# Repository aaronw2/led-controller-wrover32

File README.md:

# led-controller-wrover32
Wrover32 based LED controller for NeoPixels and DotStars with 5v signalling
and micro SD

Power:

This board is powered by 5V and generates a 3.3V supply via U1.  This board
may draw up to 500ma of current at 5V.  The 3.3V supply is capable of
generating up to 1A.

This board makes use of a Torex Semiconductor XCL220 micro DC/DC converter
to efficiently provide 3.3v of power.  This inexpensive device is reportedly
93% efficient which should increase battery life and reduce heat buildup.

Do not draw more than 500ma from any single power or ground pin on J2 or J4.

On J5, VBUS is 5V as are pins 9 and 12 on J4 and pin 1 on J2.
J6 and J7 also provide +5V at the + terminal.

5V may be shunted through the board, but limit the current to no more than 2A.

5V may be supplied by any pin, however power provided by the micro SD
connector J3 should be limited to 500 ma.

USB:

There are two USB connectors on the board for programming.  The Micro USB
connector J3 or J5 may be used.  Do not use both connectors.  J5 is designed
so either a 4 pin header or a USB cable can be soldered to the board,
eliminating the need to use micro USB.

The USB port is connected to a SI Labs CP2102 USB to serial UART for
programming and debugging purposes.

I/O:

Unlike most if not all other ESP32 based boards, this board includes a
3V to 5V bidirectional level shifter for IO25, IO26, IO32 and IO33.  These
I/O ports can also be driven by the RTC in the ESP32 to help offload driving
NeoPixels.

I/O27 is connected to an on-board SK6812MINI RGB NeoPixel with the output
connected to J2 pin 4.

Connectors:

J1: Micro SD connector

J2:
1 - VBUS (+5V)
2 - GND
3 - +3.3V
4 - DO - Output from on-board NeoPixel
5 - IO34
6 - IO33_H - IO33 at 5v signalling
7 - IO32_H - IO32 at 5V signalling
8 - IO18_H - IO18 at 5V signalling
9 - IO5_H - IO5 at 5V signalling
10 - SENSOR_VN - Input to Sensor_VN pin
11 - SENSOR_VP - Input to Sensor_VP pin
12 - Reset

J3: Micro USB connector

J4:
1 - IO23 (10K pullup)
2 - IO22 (10K pullup)
3 - IO21 (10K pullup)
4 - IO19
5 - IO26
6 - IO25
7 - IO35
8 - IO0
9 - +3.3V
10 - GND
11 - GND
12 - VBUS (+5V)

J5: USB
1 - VBUS (+5) (3A input capable)
2 - D-
3 - D+
4 - GND

J6:
1 - GND
2 - VBUS (+5V)

J7:
1 - GND
2 - VBUS (+5V)
3 - FET connected to ground, driven by IO26 (max 1A, 12V)

J8:
1 - GND
2 - IO23 (pullup) same as J4-1
3 - IO22 (pullup) same as J4-2
4 - IO21 (pullup) same as J4-3
5 - +3.3V

J9:
1 - GND
2 - +5V (3A input capable)

J11:
1 - Speaker +
2 - Speaker -

J101:
Note: pins 1 and 2 are the opposite of other power connectors
1 - +12V 400ma
2 - GND

I2C:
I2C is supported on pins IO21, IO22 and IO23, though one of those pins can
also be used for a shared interruput line.

Notes:
Some pins serve multiple purposes.  For example, two of the 5V I/O pins are
shared.  For example, IO5 is also connected to the FET for PWM and IO33 is
also connected to the BCLK on the amplifier.  If these are used, do not use
the 5V I/Os for IO5 and/or IO33.  If IO33 is used, do not hook up a speaker.

IO18 and IO32 are dedicated for 5V I/O and IO27 is dedicated for the status
LED and the output of that is useable for driving WS2812s or compatible 24-bit
LEDs.

Power:

This board uses a Torex Semiconductor XCL220 buck converter to efficiently
generate 3.3v with an output capability of up to 1A.  It supports automatic
shutdown for thermal, overcurrent and under voltage events.

Any VBUS (+5V) pin many be used to deliver or draw 5V from the board.  Total
current should not exceed 2A for all combined ground and +5V pins, however
for power input connectors J5 and J9 are capable of handling 3A in order to
supply the 12V booster

Ground:
Any GND pin can be used for ground.

+3.3V
The on-board power supply is capable of generating up to 1A.  The Wrover32 can
consume up to 500ma.  Please limit power consumption to no more than 200ma to
be safe.

+12V
This board includes a 5V to 12V boost circuit in order to provide power to
a fan or other accessories via J101.  Do not exceed 400ma.  All components
needed for the 12V boost circuit start at reference 100.  To disable 12V
support, do not install any components in this range, i.e. J101, R101, etc.

RESET:

This board can be reset in one of three ways.  The serial UART, SW1 and J2
pin 12 can all be used to reset the board.  To reset the board using J2,
pull the RESET line to ground.

5V logic

This board is designed to be able to drive 5 channels of NeoPixels, or two
channels of DotStars and one channel of NeoPixels.  One NeoPixel (D1) is
built-in to the board and the output is connected to J2 pin 4.  The other
four channels are pins J2 6, 7, 8 and 9.  Note that D1 uses a WS2813B-Mini.

Connectors J2 and J4:

Connectors J2 and J4 and JST VM12B-SRSS-TB connectors and mate with the
JST 12SR-3S connector.  These connectors can be found at Digikey, including
connectors with wires already installed. Note that the wire for the mating
connectors is a bit hard to find. Alpha Wire 2928 WH005 fits this connector.
It is a bit pricy. Mouser has it cheaper than Digikey for $35/100 feet,
though I also found it online for $25. The connector requires 7 strand wire
with an outer diameter between 0.54 and 0.58mm.

Connectors J5 and J101 are JST PH series connectors which are readily
available. J101 is not at all uncommon for computer fans.

All other connectors are pin headers with 1.27mm pitch, which is half the
normal 2.54mm pitch except for J9, which uses the 2.54mm pitch.

USB:
Use either a micro USB cable OR J5, do not use both for USB I/O.  Both,
however, are safe for power and ground, however do not exceed 900ma
when using a micro USB cable.

Microphone:

An optional SPH0645LM4H-B i2s compatible microphone is available.
If present, it is configured for the left channel.  Word-select is on IO5,
clock is on IO0 and data is on IO35.

Fan control:
The PWM pin is not near the 12v supply due to routing issues.  In order to
use PWM support, the fan must be connected to +12 or +5 and the PWM pin
(J7 pin 3) for ground. Note that J7 pin 3 should never be shorted to ground
as this will cause Q4 to act as a diode and likely burn up.

Booting and programming:
This follows the model used on the Wrover development board where DTR and
RTS are used to control IO0, IO2 and RESET.  Note that revision 1.5 and later
fixes the programming by supporting IO2.  IO2 is new for the Wrover32 and is
not used by the Wroom32.

GPIOs:
IO0: I2S-BCLK, RTS for programming, J4-8
IO2: SD-DAT0, RTS for programming
IO4: SD-DAT1
IO5: 5V I/O, FAN PWM
IO12: SD-DAT2
IO13: SD-DAT3/CD
IO14: SD-Clock
IO15: SD-Command
IO16: do not use
IO17: do not use
IO18: 5V I/O
IO19: mic I2S-WS, JU4-4
IO21: Pull-up, J4-3, SDA
IO22: Pull-up, J4-2, SCL
IO23: Pull-up, J4-1, /INT
IO25: J4-6, Speaker DIN
IO26: J4-5, Speaker BCLK
IO27: Status RGB LED output
IO32: 5V I/O
IO33: 5V I/O, Speaker LRCLK
IO34: J2-5 (input only)
IO35: MIC I2S-data in, J4-7
SENSOR_VP: J2-11
SENSOR_VN: J2-10

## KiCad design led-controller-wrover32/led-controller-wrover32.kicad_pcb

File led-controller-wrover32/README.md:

ESP32-Wrover I/Os

IO0: (reset/program), J4-8, MIC-BCLK
IO2: (reset/program), SD DAT0
IO4: SD DAT1
IO5: +5V I/O, FAN PWM
IO12: SD DAT2
IO13: SD DAT3/CD
IO14: SD CLK
IO15: SD CMD
IO16: DNC
IO17: DNC
IO18: +5V I/O
IO19: J4-4, MIC WS
IO21: I2C/INT, J4-3
IO22: I2C/INT, J4-2
IO23: I2C/INT, J4-1
IO25: J4-6, SPKR-DIN
IO26: J4-5, SPKR-BCLK
IO27: NeoPixel
IO32: +5V
IO33: +5V, SPKR-LRCLK
IO34: (input only) J2-5
IO35: (input only) J4-7, MIC-OUT
SENSOR_VP: J2-11
SENSOR_VN: J2-10
RXD0:
TXD0:
EN:

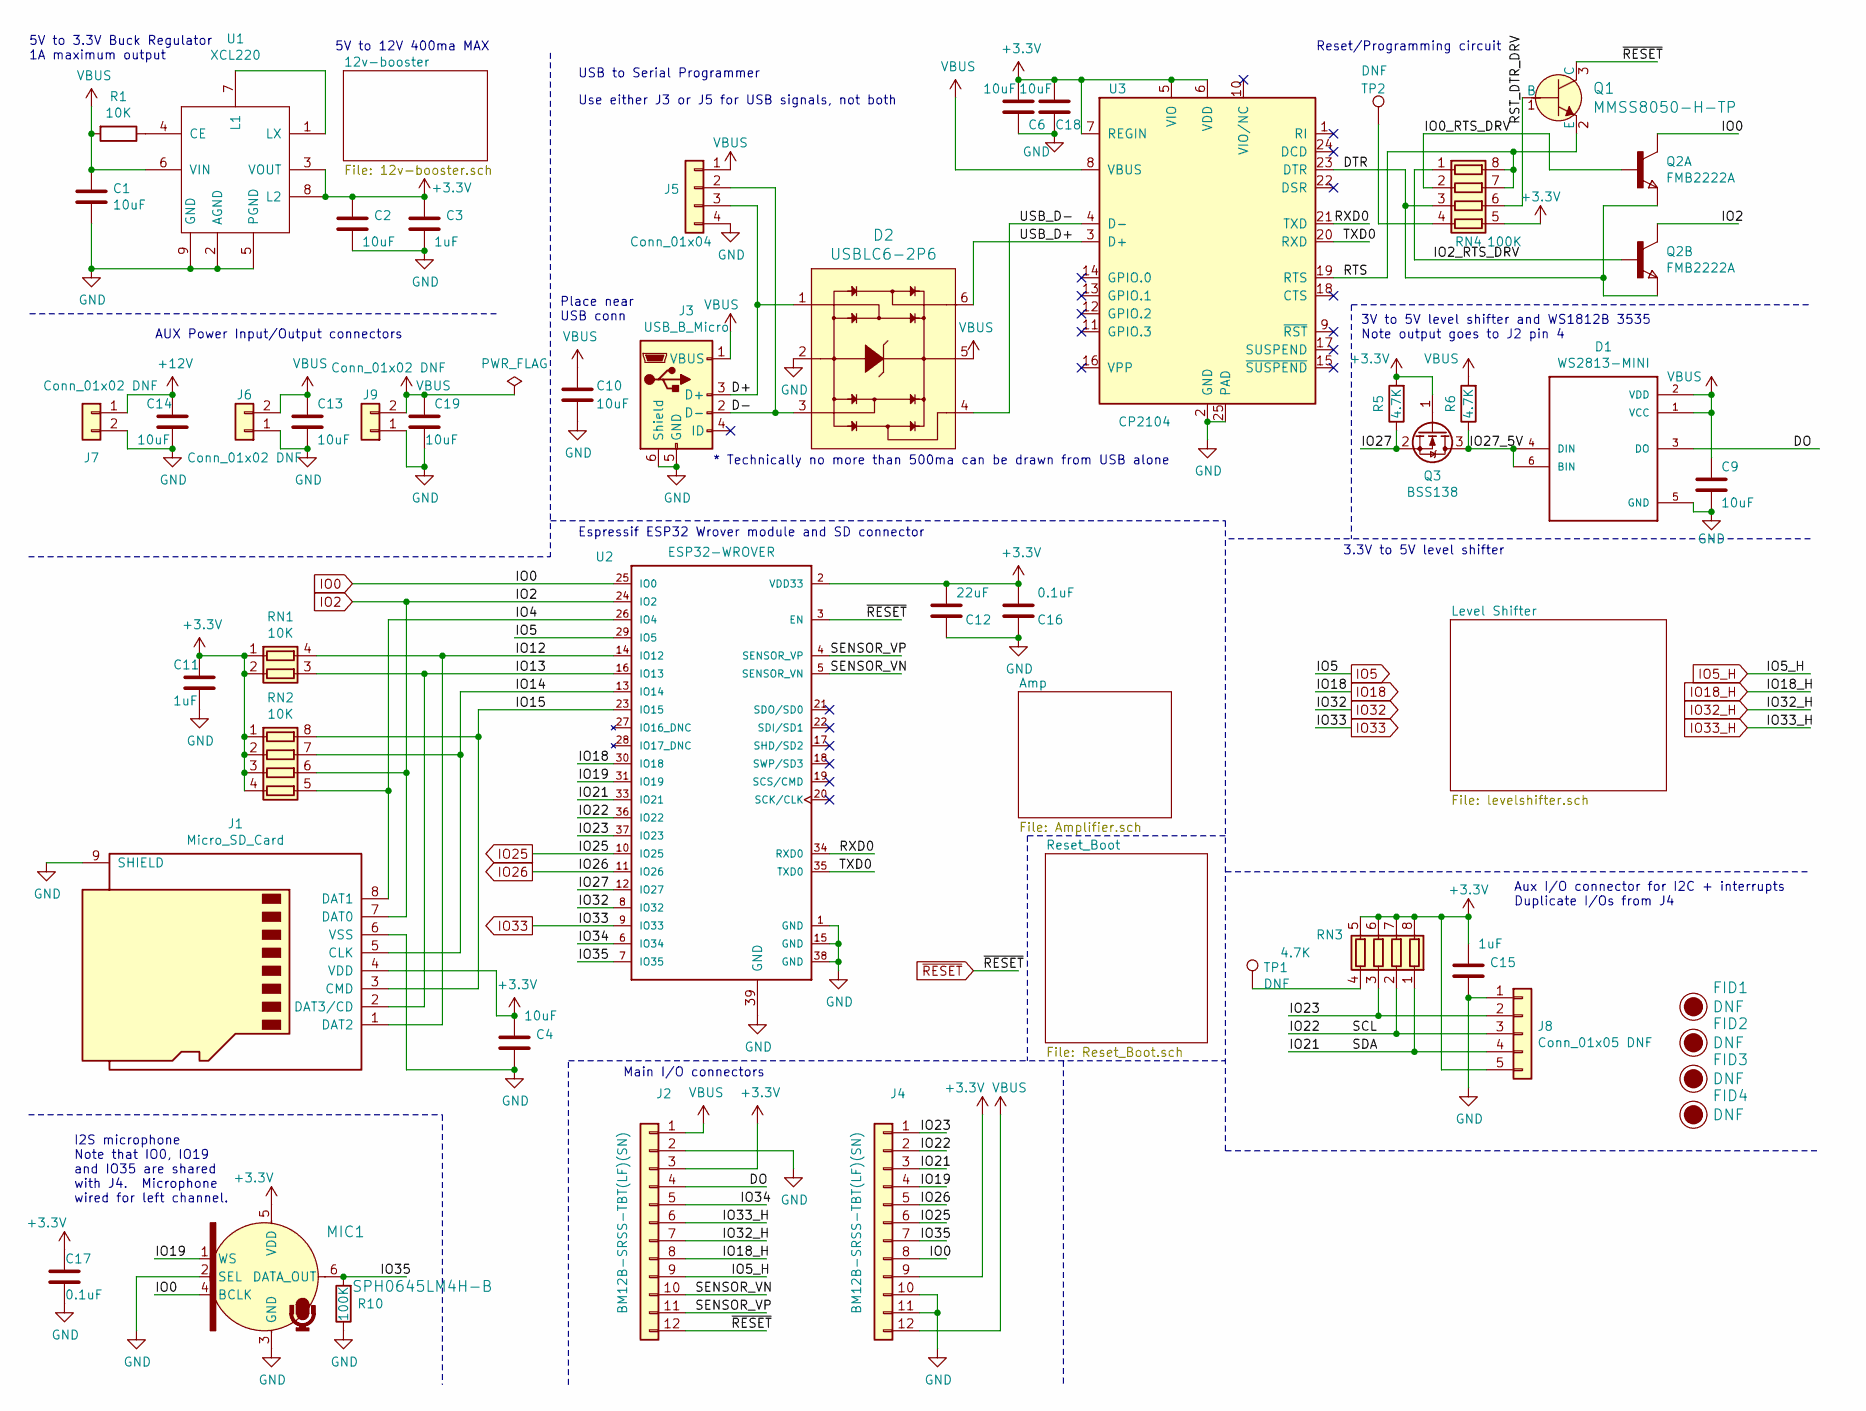
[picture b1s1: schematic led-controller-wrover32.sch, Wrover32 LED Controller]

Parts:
C1: 10uF; C_0805_2012Metric; Tolerance 20%; Minimum Voltage 10; MPN CL21B106KOQNNNE
C2, C4, C6, C9, C10, C13, C14, C18, C19: 10uF; C_0805_2012Metric; MPN CL21B106KOQNNNE
C3, C11, C15: 1uF; C_0603_1608Metric; MPN CL10B105KP8NNNC
C12: 22uF; C_0805_2012Metric; MPN CL21A226KPCLRNC
C16, C17: 0.1uF; C_0603_1608Metric; MPN GCM188R71H104KA57D
D1: WS2813-MINI; LED_WS2813-MINI-2; MPN WS2813B-Mini
D2: USBLC6-2P6; SOT-666; MPN USBLC6-2P6; Digi-Key_PN 497-5026-1-ND
FID1, FID2, FID3, FID4: DNF; Fiducial_0.5mm_Mask1mm
J1: Micro_SD_Card; microSD_HC_Wuerth_693072010801; MPN 693072010801
J2, J4: BM12B-SRSS-TBT(LF)(SN); BM12B-SRSS-TB; MPN BM12B-SRSS-TBT(LF)(SN)
J3: USB_B_Micro; USB_Micro-B_Molex-105017-0001; MPN 1050170001
J5: Conn_01x04; JST_PH_B4B-PH-K_1x04_P2.00mm_Vertical; MPN B4B-PH-K-S(LF)(SN)
J6, J7: Conn_01x02 DNF; PinHeader_1x02_P1.27mm_Vertical; MPN TMS-102-01-G-S
J8: Conn_01x05 DNF; PinHeader_1x05_P1.27mm_Vertical; MPN TMS-105-01-G-S
J9: Conn_01x02 DNF; PinHeader_1x02_P2.54mm_Vertical
MIC1: SPH0645LM4H-B; MPN SPH0645LM4H-B; Digi-Key_PN 423-1405-1-ND
Q1: MMSS8050-H-TP; SOT-23; MPN MMSS8050-H-TP; Digi-Key_PN MMSS8050-H-TPMSCT-ND
Q2: FMB2222A; SOT-23-6; MPN FMB2222A
Q3: BSS138; SOT-23; MPN BSS138
R1: 10K; R_0603_1608Metric; Tolerance 5%; MPN CRCW060310K0FKEC
R5, R6: 4.7K; R_0603_1608Metric; MPN CR0603-FX-4701ELF
R10: 100K; R_0603_1608Metric; MPN CRCW0603100KJNEA
RN1: 10K; R_Array_Convex_2x0603; MPN EXB-V4V103JV
RN2: 10K; R_Array_Convex_4x0603; MPN EXB-V8V103JV
RN3: 4.7K; R_Array_Convex_4x0603; MPN CAT16-4701F4LF
RN4: 100K; R_Array_Convex_4x0603; MPN EXB-V8V104JV
TP1, TP2: DNF; TestPoint_Pad_D1.0mm
U1: XCL220; CL-2025-02; MPN XCL220B333FR-G
U2: ESP32-WROVER; ESP32-WROOVER; MPN ESP32-WROVER (16MB)
U3: CP2104; QFN-24-1EP_4x4mm_P0.5mm_EP2.6x2.6mm; MPN CP2104-F03-GMR

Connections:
+3V3: C2.1, C3.1, C4.1, C6.1, C11.1, C12.1, C15.1, C16.1, C17.1, C18.1, J1.4 (VDD), J2.3, J4.9, J8.5, MIC1.5 (VDD), Q3.1 (G), R5.2, RN1.1 (R1.1), RN1.2 (R2.1), RN2.1 (R1.1), RN2.2 (R2.1), RN2.3 (R3.1), RN2.4 (R4.1), RN3.5 (R4.2), RN3.6 (R3.2), RN3.7 (R2.2), RN3.8 (R1.2), RN4.5 (R4.2), U1.3 (VOUT), U1.8 (L2), U2.2 (VDD33), U3.5 (VIO), U3.6 (VDD), U3.7 (REGIN); also elsewhere on the board
+12V: C14.1, J7.1; also elsewhere on the board
/D+: D2.1, J3.3 (D+), J5.3
/D-: D2.3, J3.2 (D-), J5.2
/DO: D1.3 (DO), J2.4
/DTR: Q2.2 (E), Q2.5 (E), RN4.3 (R3.1), U3.23 (DTR)
/IO0_RTS_DRV: Q2.1 (B), RN4.2 (R2.1)
/IO2_RTS_DRV: Q2.3 (B), RN4.1 (R1.1)
/IO4: J1.8 (DAT1), RN2.5 (R4.2), U2.26 (IO4)
/IO12: J1.1 (DAT2), RN1.4 (R1.2), U2.14 (IO12)
/IO13: J1.2 (DAT3/CD), RN1.3 (R2.2), U2.16 (IO13)
/IO14: J1.5 (CLK), RN2.7 (R2.2), U2.13 (IO14)
/IO15: J1.3 (CMD), RN2.8 (R1.2), U2.23 (IO15)
/IO19: J4.4, MIC1.1 (WS), U2.31 (IO19)
/IO21: J4.3, J8.4, RN3.1 (R1.1), U2.33 (IO21)
/IO22: J4.2, J8.3, RN3.2 (R2.1), U2.36 (IO22)
/IO23: J4.1, J8.2, RN3.3 (R3.1), U2.37 (IO23)
/IO27: Q3.2 (S), R5.1, U2.12 (IO27)
/IO27_5V: D1.4 (DIN), D1.6 (BIN), Q3.3 (D), R6.1
/IO34: J2.5, U2.6 (IO34)
/IO35: J4.7, MIC1.6 (DATA_OUT), R10.2, U2.7 (IO35)
/RST_DTR_DRV: Q1.1 (B), RN4.6 (R3.2)
/RTS: Q1.2 (E), RN4.7 (R2.2), RN4.8 (R1.2), U3.19 (RTS)
/RXD0: U2.34 (RXD0), U3.21 (TXD)
/SENSOR_VN: J2.10, U2.5 (SENSOR_VN)
/SENSOR_VP: J2.11, U2.4 (SENSOR_VP)
/TXD0: U2.35 (TXD0), U3.20 (RXD)
/USB_D+: D2.6, U3.3 (D+)
/USB_D-: D2.4, U3.4 (D-)
GND: C1.2, C2.2, C3.2, C4.2, C6.2, C9.2, C10.2, C11.2, C12.2, C13.2, C14.2, C15.2, C16.2, C17.2, C18.2, C19.2, D1.5 (GND), D2.2, J1.6 (VSS), J1.9 (SHIELD), J2.2, J3.5 (GND), J3.6 (Shield), J4.10, J4.11, J5.4, J6.1, J7.2, J8.1, J9.1, MIC1.2 (SEL), MIC1.3 (GND), R10.1, U1.2 (AGND), U1.5 (PGND), U1.9 (GND), U2.1 (GND), U2.15 (GND), U2.38 (GND), U2.39 (GND), U3.2 (GND), U3.25 (PAD); also elsewhere on the board
IO0: J4.8, MIC1.4 (BCLK), Q2.6 (C), U2.25 (IO0); also elsewhere on the board
IO2: J1.7 (DAT0), Q2.4 (C), RN2.6 (R3.2), U2.24 (IO2); also elsewhere on the board
IO5: U2.29 (IO5); also elsewhere on the board
IO5_H: J2.9; also elsewhere on the board
IO18: U2.30 (IO18); also elsewhere on the board
IO18_H: J2.8; also elsewhere on the board
IO25: J4.6, U2.10 (IO25); also elsewhere on the board
IO26: J4.5, U2.11 (IO26); also elsewhere on the board
IO32: U2.8 (IO32); also elsewhere on the board
IO32_H: J2.7; also elsewhere on the board
IO33: U2.9 (IO33); also elsewhere on the board
IO33_H: J2.6; also elsewhere on the board
unnamed: R1.1, U1.4 (CE)
unnamed: RN3.4 (R4.1), TP1.1
unnamed: RN4.4 (R4.1), TP2.1
unnamed: U1.1 (LX), U1.7 (L1)
VBUS: C1.1, C9.1, C10.1, C13.1, C19.1, D1.1 (VCC), D1.2 (VDD), D2.5, J2.1, J3.1 (VBUS), J4.12, J5.1, J6.2, J9.2, R1.2, R6.2, U1.6 (VIN), U3.8 (VBUS); also elsewhere on the board
~RESET: J2.12, Q1.3 (C), U2.3 (EN); also elsewhere on the board

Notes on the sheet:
3.3V to 5V level shifter
Place near USB conn
5V to 3.3V Buck Regulator 1A maximum output
AUX Power Input/Output connectors
USB to Serial Programmer
Use either J3 or J5 for USB signals, not both
* Technically no more than 500ma can be drawn from USB alone
Reset/Programming circuit
I2S microphone Note that IO0, IO19 and IO35 are shared with J4. Microphone wired for left channel.
Main I/O connectors
Aux I/O connector for I2C + interrupts Duplicate I/Os from J4
Espressif ESP32 Wrover module and SD connector
5V to 12V 400ma MAX
3V to 5V level shifter and WS1812B 3535 Note output goes to J2 pin 4

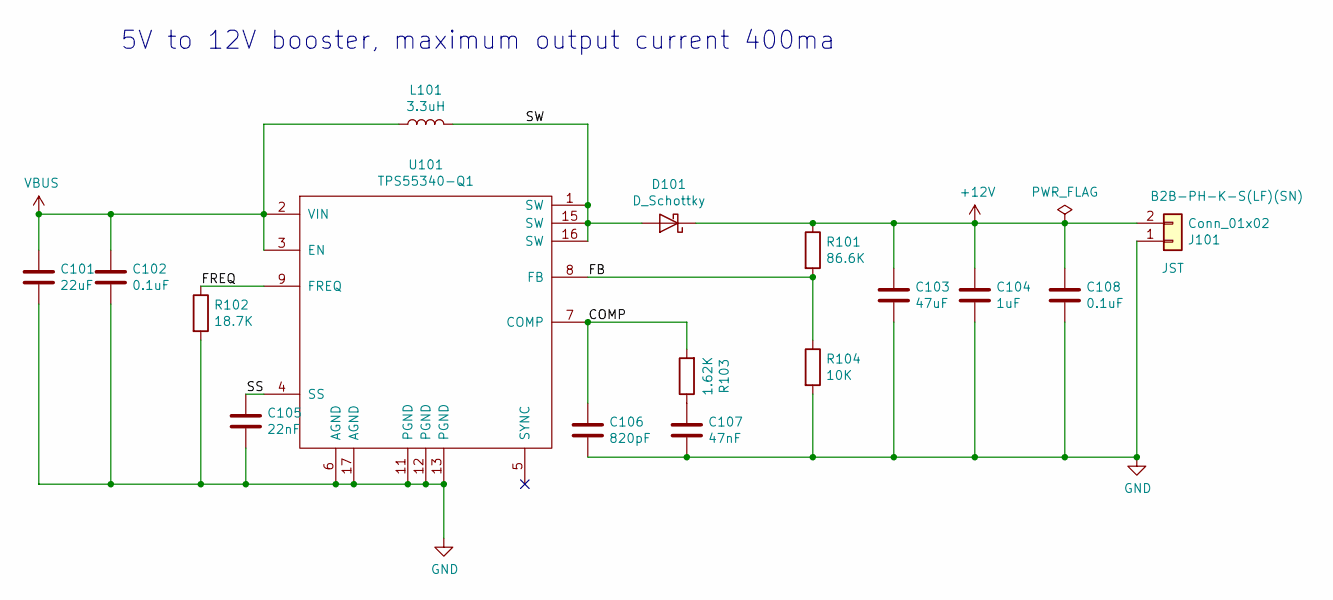
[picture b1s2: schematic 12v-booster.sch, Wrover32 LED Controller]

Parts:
C101: 22uF; C_0603_1608Metric; MPN CL10A226MO7JZNC
C102, C108: 0.1uF; C_0603_1608Metric; MPN GCM188R71H104KA57D
C103: 47uF; C_1210_3225Metric; MPN CL32A476KOJNNNE
C104: 1uF; C_0603_1608Metric; MPN CL10B105KP8NNNC
C105: 22nF; C_0603_1608Metric; MPN CC0603JRX7R9BB223
C106: 820pF; C_0603_1608Metric; MPN CC0603JRNPO9BN821
C107: 47nF; C_0603_1608Metric; MPN GRM188R61H474KA12D
D101: D_Schottky; D_SOD-123F; MPN SS24FL
J101: Conn_01x02; JST_PH_B2B-PH-K_1x02_P2.00mm_Vertical; MPN B2B-PH-K-S(LF)(SN)
L101: 3.3uH; L_Vishay_IHLP-1212; MPN IHLP1212BZER3R3M11
R101: 86.6K; R_0603_1608Metric; MPN CRCW060386K6FKEA
R102: 18.7K; R_0603_1608Metric; MPN RC0603FR-0718K7L
R103: 1.62K; R_0603_1608Metric; MPN RC0603FR-071K62L
R104: 10K; R_0603_1608Metric; MPN CRCW060310K0FKEC
U101: TPS55340-Q1; QFN-16-1EP_3x3mm_P0.5mm_EP2.7x2.7mm_ThermalVias; MPN TPS55340RTER

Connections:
+12V: C103.1, C104.1, C108.1, D101.1 (K), J101.2, R101.1; also elsewhere on the board
/12v-booster/COMP: C106.1, R103.2, U101.7 (COMP)
/12v-booster/FB: R101.2, R104.1, U101.8 (FB)
/12v-booster/FREQ: R102.1, U101.9 (FREQ)
/12v-booster/SS: C105.1, U101.4 (SS)
/12v-booster/SW: D101.2 (A), L101.2, U101.1 (SW), U101.15 (SW), U101.16 (SW)
GND: C101.2, C102.2, C103.2, C104.2, C105.2, C106.2, C107.2, C108.2, J101.1, R102.2, R104.2, U101.6 (AGND), U101.11 (PGND), U101.12 (PGND), U101.13 (PGND), U101.17 (AGND); also elsewhere on the board
unnamed: C107.1, R103.1
VBUS: C101.1, C102.1, L101.1, U101.2 (VIN), U101.3 (EN); also elsewhere on the board

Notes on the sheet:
5V to 12V booster, maximum output current 400ma

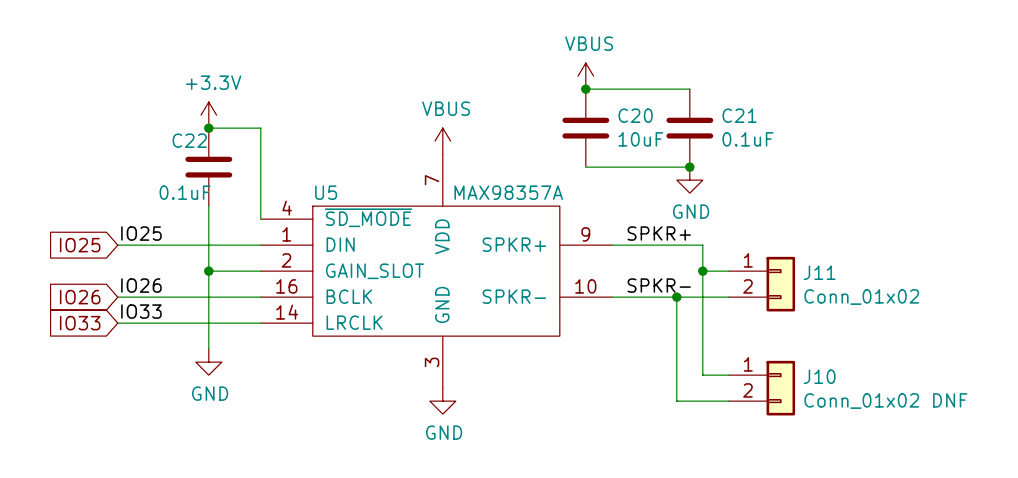
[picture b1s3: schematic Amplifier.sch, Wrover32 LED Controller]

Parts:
C20: 10uF; C_0805_2012Metric; MPN CL21B106KOQNNNE
C21, C22: 0.1uF; C_0603_1608Metric; MPN GCM188R71H104KA57D
J10: Conn_01x02 DNF; PinHeader_1x02_P1.27mm_Vertical_SMD_Pin1Left; MPN M50-3630242R
J11: Conn_01x02; JST_SH_BM02B-SRSS-TB_1x02-1MP_P1.00mm_Vertical; MPN BM02B-SRSS-TB(LF)(SN)
U5: MAX98357A; VQFN-16-1EP_3x3mm_P0.5mm_EP1.68x1.68mm; MPN MAX98357AETE+T

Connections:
+3V3: C22.1, U5.4 (~SD_MODE); also elsewhere on the board
/Amp/SPKR+: J10.1, J11.1, U5.9 (SPKR+)
/Amp/SPKR-: J10.2, J11.2, U5.10 (SPKR-)
GND: C20.2, C21.2, C22.2, U5.2 (GAIN_SLOT), U5.3 (GND), U5.11 (GND), U5.15 (GND), U5.17 (GND); also elsewhere on the board
IO25: U5.1 (DIN); also elsewhere on the board
IO26: U5.16 (BCLK); also elsewhere on the board
IO33: U5.14 (LRCLK); also elsewhere on the board
VBUS: C20.1, C21.1, U5.7 (VDD), U5.8 (VDD); also elsewhere on the board

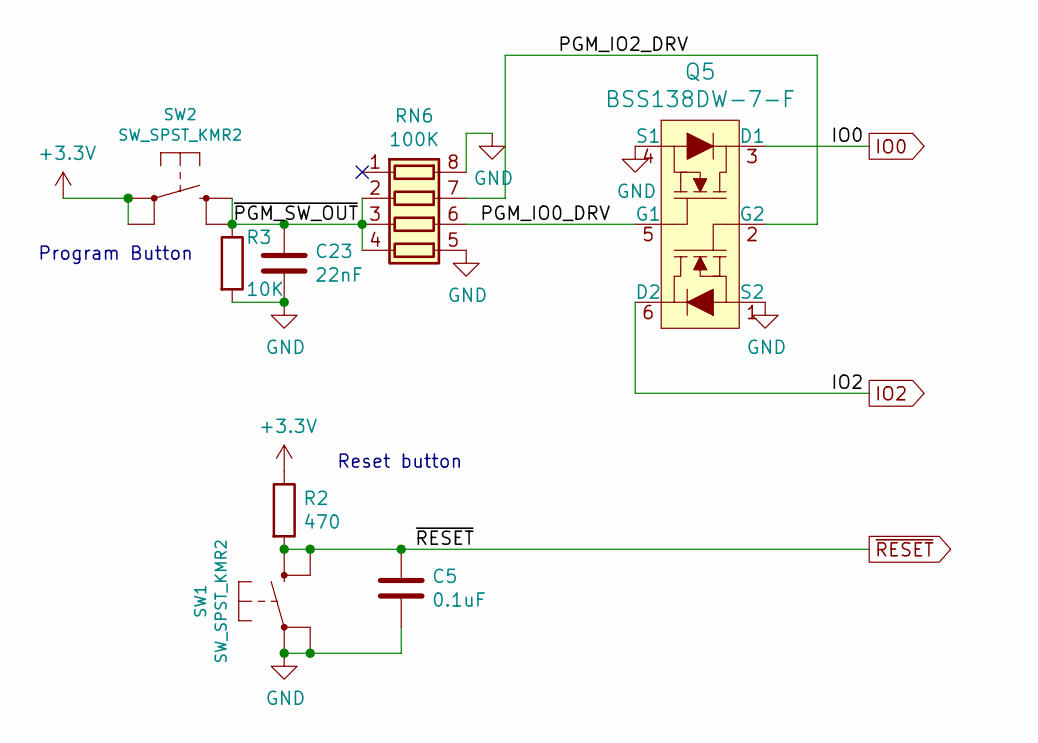
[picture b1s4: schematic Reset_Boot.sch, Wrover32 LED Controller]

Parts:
C5: 0.1uF; C_0603_1608Metric; MPN GCM188R71H104KA57D
C23: 22nF; C_0603_1608Metric; MPN CC0603JRX7R9BB223
Q5: BSS138DW-7-F; SOT-363_SC-70-6; MPN BSS138DW-7-F; Digi-Key_PN BSS138DW-FDICT-ND
R2: 470; R_0603_1608Metric; MPN RC1608F471CS
R3: 10K; R_0603_1608Metric; MPN CRCW060310K0FKEC
RN6: 100K; R_Array_Convex_4x0603; MPN EXB-V8V104JV
SW1, SW2: SW_SPST_KMR2; MPN KMR211GLFS

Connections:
+3V3: R2.1, SW2.1; also elsewhere on the board
/Reset_Boot/PGM_IO0_DRV: Q5.5 (G1), RN6.6 (R3.2)
/Reset_Boot/PGM_IO2_DRV: Q5.2 (G2), RN6.7 (R2.2)
/Reset_Boot/~PGM_SW_OUT: C23.1, R3.1, RN6.2 (R2.1), RN6.3 (R3.1), RN6.4 (R4.1), SW2.2 (S)
GND: C5.2, C23.2, Q5.1 (S2), Q5.4 (S1), R3.2, RN6.5 (R4.2), RN6.8 (R1.2), SW1.1; also elsewhere on the board
IO0: Q5.3 (D1); also elsewhere on the board
IO2: Q5.6 (D2); also elsewhere on the board
~RESET: C5.1, R2.2, SW1.2 (S); also elsewhere on the board

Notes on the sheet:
Reset button
Program Button

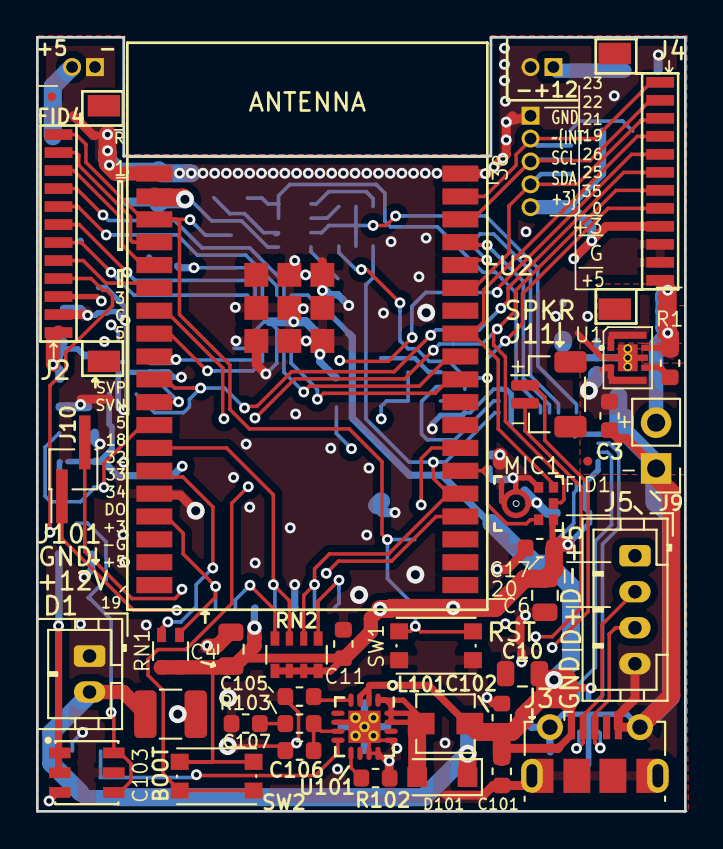
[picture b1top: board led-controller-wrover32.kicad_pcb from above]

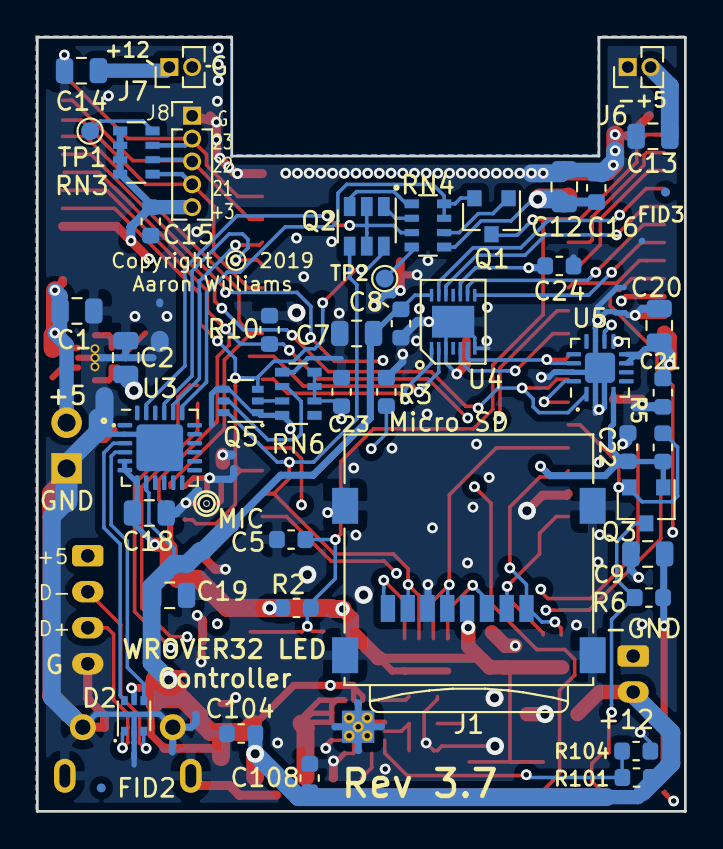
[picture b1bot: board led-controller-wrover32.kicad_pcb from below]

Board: 4 copper layers, 36.0 x 43.0 mm, 82 parts (46 on the bottom side), 59 nets.

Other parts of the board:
C7: 10uF; C_0805_2012Metric
C8, C24: 0.1uF; C_0603_1608Metric
U4: MAX3379EETD; TDFN-14_3x3mm_P0.4mm_EP1.78x2.35mm

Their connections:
+3V3: C24.1, U4.10; also elsewhere on the board
GND: C7.2, C8.2, C24.2, U4.3, U4.7, U4.15; also elsewhere on the board
IO5: U4.1; also elsewhere on the board
IO5_H: U4.13; also elsewhere on the board
IO18: U4.2; also elsewhere on the board
IO18_H: U4.12; also elsewhere on the board
IO32: U4.5; also elsewhere on the board
IO32_H: U4.9; also elsewhere on the board
IO33: U4.6; also elsewhere on the board
IO33_H: U4.8; also elsewhere on the board
VBUS: C7.1, C8.1, U4.14; also elsewhere on the board

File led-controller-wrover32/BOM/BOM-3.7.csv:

Refs,Value,Footprint,Quantity,DESC,MFR,MPN,SPR,SPN,SPURL
J11,Conn_01x02,Aaron:JST_SH_BM02B-SRSS-TB_1x02-1MP_P1.00mm_Vertical,1,CONN HEADER SMD 2POS 1MM,JST Sales America Inc.,BM02B-SRSS-TB(LF)(SN),Digikey,455-1788-1-ND,https://www.digikey.com/product-detail/en/jst-sales-america-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
L101,3.3uH,Aaron:L_Vishay_IHLP-1212,1,FIXED IND 3.3UH 2.7A 61 MOHM SMD,Vishay Dale,IHLP1212BZER3R3M11,Digikey,541-2567-1-ND,-
U101,TPS55340-Q1,Aaron:QFN-16-1EP_3x3mm_P0.5mm_EP2.7x2.7mm_ThermalVias,1,IC REG BOOST ADJ 5.25A 16WQFN,Texas Instruments,TPS55340RTER,Digikey,296-37677-1-ND,-
MIC1,SPH0645LM4H-B,Aaron:SPH0645LM4H-B,1,CRAWFORD MIC DGT I2S BOTTOM PORT,Knowles,SPH0645LM4H-B,Digikey,423-1405-1-ND,https://www.digikey.com/products/en/audio-products/microphon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
SW2;SW1,SW_SPST_KMR2,Aaron:SW_SPST_KMR2,2,SWITCH TACTILE SPST-NO 0.05A 32V,C&K,KMR211GLFS,Digikey,401-1426-1-ND,https://www.digikey.com/product-detail/en/c-k/KMR211GLFS/401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
U4,MAX3379EETD,Aaron:TDFN-14_3x3mm_P0.4mm_EP1.78x2.35mm,1,"Translation - Voltage Levels 15kV ESD-Protected, 1 A, 16Mbps, Dual/Quad Low-Voltage Level Translators in UCSP",Maxim Integrated,MAX3379EETD+,Mouser,700-MAX3379EETD+,https://www.mouser.com/ProductDetail/Maxim-Integrated/MAX337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
J3,USB_B_Micro,Aaron:USB_Micro-B_Molex-105017-0001,1,CONN RCPT USB2.0 MICRO B SMD R/A,Molex,1050170001,Digikey,WM1399CT-ND,-
U5,MAX98357A,Aaron:VQFN-16-1EP_3x3mm_P0.5mm_EP1.68x1.68mm,1,IC AMP CLASS D MONO 3.2W 16TQFN,Maxim Integrated,MAX98357AETE+T,Digikey,MAX98357AETE+TCT-ND,https://www.digikey.com/products/en/integrated-circuits-ics/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
J1,Micro_SD_Card,Aaron:microSD_HC_Wuerth_693072010801,1,CONN MICRO SD CARD HINGED TYPE,Wuerth,693072010801,Digikey,732-3820-1-ND,https://www.digikey.com/product-detail/en/w-rth-elektronik/6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
C16;C17;C108;C102;C21;C22;C5;C24;C8,0.1uF,Capacitor_SMD:C_0603_1608Metric,9,CAP CER 0.1UF 50V X7R 0603,Murata Electronics,GCM188R71H104KA57D,Digikey,490-4779-1-ND,https://www.digikey.com/product-detail/en/murata-electronics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
C3;C11;C15;C104,1uF,Capacitor_SMD:C_0603_1608Metric,4,CAP CER 1UF 10V X7R 0603,Samsung,CL10B105KP8NNNC,Digikey,1276-1946-1-ND,-
C105;C23,22nF,Capacitor_SMD:C_0603_1608Metric,2,CAP CER 0.022UF 50V X7R 0603,Yageo,CC0603JRX7R9BB223,Digikey,311-4010-1-ND,https://www.digikey.com/product-detail/en/yageo/CC0603JRX7R9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
C101,22uF,Capacitor_SMD:C_0603_1608Metric,1,CAP CER 22UF 16V X5R 0603,Samsung Electro-Mechanics,CL10A226MO7JZNC,Digikey,1276-7076-1-ND,https://www.digikey.com/products/en/capacitors/ceramic-capac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
C107,47nF,Capacitor_SMD:C_0603_1608Metric,1,CAP CER 0.47UF 50V X5R 0603,Murata,GRM188R61H474KA12D,Digikey,490-11994-1-ND,-
C106,820pF,Capacitor_SMD:C_0603_1608Metric,1,CAP CER 820PF 50V C0G/NPO 0603,Yageo,CC0603JRNPO9BN821,Digikey,311-1775-1-ND,https://www.digikey.com/products/en?keywords=311-1775-1-ND
C1;C2;C6;C4;C10;C13;C14;C19;C9;C18;C20;C7,10uF,Capacitor_SMD:C_0805_2012Metric,12,CAP CER 10UF 16V X7R 0805,Samsung,CL21B106KOQNNNE,Digikey,1276-2872-1-ND,-
C12,22uF,Capacitor_SMD:C_0805_2012Metric,1,CAP CER 22UF 10V X5R 0805,Samsung,CL21A226KPCLRNC,Digikey,1276-6786-1-ND,https://www.digikey.com/product-detail/en/samsung-electro-me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
C103,47uF,Capacitor_SMD:C_1210_3225Metric,1,CAP CER 47UF 16V X5R 1210,Samsung,CL32A476KOJNNNE,Digikey,1276-3376-1-ND,https://www.digikey.com/product-detail/en/samsung-electro-me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
J101,Conn_01x02,Connector_JST:JST_PH_B2B-PH-K_1x02_P2.00mm_Vertical,1,CONN HEADER VERT 2POS 2MM,JST,B2B-PH-K-S(LF)(SN),Digikey,455-1704-ND,https://www.digikey.com/product-detail/en/jst-sales-america-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
J5,Conn_01x04,Connector_JST:JST_PH_B4B-PH-K_1x04_P2.00mm_Vertical,1,CONN HEADER VERT 4POS 2MM,JST Sales America,B4B-PH-K-S(LF)(SN),Digikey,455-1706-ND,-
J4;J2,BM12B-SRSS-TBT(LF)(SN),Connectors_JST-BM12B-SURS-TF:BM12B-SRSS-TB,2,CONN HEADER SMD 12POS 1MM,JST,BM12B-SRSS-TBT(LF)(SN),Digikey,455-2960-1-ND,https://www.digikey.com/products/en/connectors-interconnects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
D101,D_Schottky,Diode_SMD:D_SOD-123F,1,DIODE SCHOTTKY 40V 2A SOD123F,ON,SS24FL,Digikey,SS24FLCT-ND,-
U2,ESP32-WROVER,ESP32:ESP32-WROOVER,1,WIFI MODULE 128MBITS SPI FLASH,Espressif Systems,ESP32-WROVER (16MB),Digikey,1904-1015-1-ND,https://www.digikey.com/product-detail/en/espressif-systems/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
D1,WS2813-MINI,LED_WS2813-mini:LED_WS2813-MINI-2,1,"RGB 620~625nm Red, 515~525nm Green, 465~475nm Blue SMD-6 Light Emitting Diodes (LED) RoHS",World Semi,WS2813B-Mini,LCSC,C189639,https://lcsc.com/product-detail/Light-Emitting-Diodes-LED_Wo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
U3,CP2104,Package_DFN_QFN:QFN-24-1EP_4x4mm_P0.5mm_EP2.6x2.6mm,1,IC SGL USB-TO-UART BRIDGE 24QFN,Silicon Labs,CP2104-F03-GMR,Digikey,336-4146-1-ND,https://www.digikey.com/products/en/integrated-circuits-ics/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
Q3,BSS138,Package_TO_SOT_SMD:SOT-23,1,N-Channel 50V 220mA (Ta) 360mW (Ta) Surface Mount SOT-23-3,ON Semiconductor,BSS138,Digikey,BSS138CT-ND,-
Q1,MMSS8050-H-TP,Package_TO_SOT_SMD:SOT-23,1,TRANS NPN 25V 1.5A SOT23,Micro Commercial Co,MMSS8050-H-TP,Digikey,MMSS8050-H-TPMSCT-ND,https://www.digikey.com/products/en/discrete-semiconductor-p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
Q2,FMB2222A,Package_TO_SOT_SMD:SOT-23-6,1,TRANS 2NPN 40V 0.5A 6SSOT,ON Semiconductor,FMB2222A,Digikey,FMB2222ACT-ND,-
Q5,BSS138DW-7-F,Package_TO_SOT_SMD:SOT-363_SC-70-6,1,MOSFET 2N-CH 50V 0.2A SC70-6,Diodes Incorporated,BSS138DW-7-F,Digikey,BSS138DW-FDICT-ND,https://www.digikey.com/products/en/discrete-semiconductor-p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
D2,USBLC6-2P6,Package_TO_SOT_SMD:SOT-666,1,TVS DIODE 5.25V 17V SOT666,ST Microelectronics,USBLC6-2P6,Digikey,497-5026-1-ND,-
R103,1.62K,Resistor_SMD:R_0603_1608Metric,1,RES SMD 1.62K OHM 1% 1/10W 0603,Yageo,RC0603FR-071K62L,Digikey,311-1.62KHRCT-ND,https://www.digikey.com/product-detail/en/yageo/RC0603FR-071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
R10,100K,Resistor_SMD:R_0603_1608Metric,1,RES SMD 100K OHM 5% 1/10W 0603,Vishay Dale,CRCW0603100KJNEA,Digikey,541-100KGCT-ND,-
R1;R104;R3,10K,Resistor_SMD:R_0603_1608Metric,3,RES SMD 10K OHM 1% 1/10W 0603,Vishay Dale,CRCW060310K0FKEC,Digikey,541-2979-1-ND,-
R102,18.7K,Resistor_SMD:R_0603_1608Metric,1,RES SMD 18.7K OHM 1% 1/10W 0603,Yageo,RC0603FR-0718K7L,Digikey,311-18.7KHRCT-ND,https://www.digikey.com/product-detail/en/yageo/RC0603FR-071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
R5;R6,4.7K,Resistor_SMD:R_0603_1608Metric,2,RES SMD 4.7K OHM 1% 1/10W 0603,Bourns Inc.,CR0603-FX-4701ELF,Digikey,CR0603-FX-4701ELFCT-ND,https://www.digikey.com/product-detail/en/bourns-inc/CR0603-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
R2,470,Resistor_SMD:R_0603_1608Metric,1,RES SMD 470 OHM 1% 1/10W 0603,Samsung,RC1608F471CS,Digikey,1276-4619-1-ND,-
R101,86.6K,Resistor_SMD:R_0603_1608Metric,1,RES SMD 86.6K OHM 1% 1/10W 0603,Vishay Dale,CRCW060386K6FKEA,Digikey,541-86.6KHCT-ND,-
RN1,10K,Resistor_SMD:R_Array_Convex_2x0603,1,"10k Ohm +/- 5% Isolated  Resistor Network, 0606, Concave",Panasonic,EXB-V4V103JV,Digikey,Y2103CT-ND,-
RN4;RN6,100K,Resistor_SMD:R_Array_Convex_4x0603,2,RES ARRAY 4 RES 100K OHM 1206,Panasonic,EXB-V8V104JV,Digikey,Y4104CT-ND,https://www.digikey.com/product-detail/en/panasonic-electron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
RN2,10K,Resistor_SMD:R_Array_Convex_4x0603,1,RES ARRAY 4 RES 10K OHM 1206,Panasonic,EXB-V8V103JV,Digikey,Y4103CT-ND,-
RN3,4.7K,Resistor_SMD:R_Array_Convex_4x0603,1,RES ARRAY 4 RES 4.7K OHM 1206,Bourns Inc.,CAT16-4701F4LF,Digikey,CAT16-4701F4LFCT-ND,https://www.digikey.com/product-detail/en/bourns-inc/CAT16-4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
U1,XCL220,Torex_Semi:CL-2025-02,1,DC DC CONVERTER 3.3V,Torex Semiconductor,XCL220B333FR-G,Digikey,893-1279-1-ND,-

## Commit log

2018-09-09 Initial checkin of Espressif Wrover32 LED controller board
2018-09-09 Added very early draft of README.
2018-09-09 Some minor cleanup.
    - Moved power trace too close to ground pad for ESP32.
    - Fixed silkscreen for J2 and J4 and moved some references and text.
2018-09-09 Changed page size to Letter instead of A4.
2018-09-10 Fixed footprint for NeoPixel.
2018-09-10 I updated a few more things.
    - Slightly re-arranged the connectors so 5v isn't next to 3v and 3v I/O
    - Fixed footprints for NeoPixel MINI and power supply
    - Added a power supervisor chip
    - Some routing improvements
2018-09-13 I changed some part numbers and fixed the solder paste for the connectors.
2018-09-18 Revision 1.1.1, moved things around a little.
2018-09-20 - Added some more I/O pins to J4 and added pull-up resistors to IO21, IO22 and IO23. - Cleaned up Torex buck converter - Minor layout changes - Added more ground vias near the antenna. - Added anothe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
2018-09-20 Did some more trace cleanup.
2018-09-20 Updated README.MD with more info
    Added more information. All info is related to version 1.2 of the board
2018-09-21 Forgot to check in this file to 1.2
2018-09-21 Fixed some silkscreen issues.
2018-09-21 Fixed several issues.
    1. GPIOs 16 and 17 should not be connected.
    2. GPIO 35 was mislabeled GPIO36. It's input only and would not have
    been able to drive the TS pin oin the MAX chip.
    3. Routed GPIO35 to J4.
    4. Added a 0.1uF bypass capacitor for Wrover32 like the datasheet recommends.
    5. Added another 3.3v pin to J4 after removing GPIOs 16 and 17.
2018-09-23 Added microphone and updated README
2018-09-23 Changed the connectors from JST to a TE 1-1734595-2 connector.
    This connector uses crimped on pins, but it may be easier to deal
    with since it works with 28 gauge wire whereas the JST requires 30
    gauge (though I ordered some 28AWG that should fit it).
    This can always be reverted.
2018-10-04 Finalized v1.4 design.
    Added USB protection diodes.
    Cleaned up routing some more.
    Cleaned up the silk screening after getting connector models.
2018-10-11 Minor cleanup. - Removed overlapping fiducials (which aren't really needed) - Changed 3 pull-up resistors for IO21, IO22 and IO23 to use a resistor network and moved further away from J8 - Fixed unco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
2018-10-11 Fixed solder mask clearance.
2018-10-14 - Cleaned up the schematic - Made J5 USB D+ and D- go through protection diodes
2018-11-06 Fixed (hopefully) the ws1812b 3535 footprint.
2018-11-10 This fixes a number of issues: - IO2 is now set according to the DTR and RTS signals. This is required for booting over the serial port. - Some more footprints were found to be using the old Kicad 4 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
2018-11-10 Added 12v boost supply and enlarged board.
    This branch and initial commit enlarges the board in order to add a 5V to
    12V boost switching supply which can provide up to 400ma of current.
    Additionally, J5 was changed to a JST PH connector and J9 and J101 were
    added. All 12V boost supply components start at 100. Due to the
    addition of the boost switching supply, the length of the board was
    increased.
2018-11-10 Updated README.md to document changes and fixes in revision 2.0
2018-11-10 Updated README.md and added BOM. Note that there were no changes to the board layout.
2018-11-10 Added BOM and also fixed missing value for RN3
2018-11-10 Fixed value for RN3 and fidicial references and added rescue files.
2019-01-26 Fixed solder mask padding.
2019-01-26 Oops, changed the wrong thing, this fixes it.
2019-05-23 2.1.0: Changed NeoPixel to WS2813B-Mini
    This replaces the SK6812-3535 with a WS2813B-Mini. The mini is able to
    dissipate heat better.
    Also upgraded KiCad to 5.1.2.
    Added teardrops to vias.
    BOM updated with J5 fixed.
    NOTE: The WS2813B-Mini footprint has not yet been tested. This is a custom
2019-10-30 Version 3.0.0
    - Added speaker output support
    - Added 22 ohm resistors on 5V I/O
    - Changed from 2 to 4 layers
    - Added boot button
    - Added 12V to PWM output
    - Added 5V protection diode
2019-10-30 Updated to version 3.0.0
    - Added boot button for programming
    - Added speaker output
    - Added protection diode for 5V
    - Fixed USB program and reset circuit to match development board
    - Made board 4 layers
    - Changed voltage at PWM output from 5V to 12V
2019-11-15 Fixed microphone, fan PWM and speaker
    The ground was not hooked up to the microphone due to an issue with the
    footprint.
    The PWM pin was also used by the microphone. Moved PWM pin to IO 5 which is
    also shared with 5V output.
    The speaker LR clock was using IO34 which is input only. Moved to IO33 which
    is also shared with a 5V output.
2019-11-16 Minor cleanup
2019-11-16 Fixed serial interface, TX and RX were swapped
    Added additional ground around the antenna to the power plane
    Minor cleanups
2019-11-16 Minor changes.
2019-11-16 Minor fixup for filled areas.
2019-11-16 Fix the microphone footprint and other minor cleanup. Note that this updates the stencil but the old stencil should still work without issues.
    Rev 3.0.4
2019-11-23 Changed output 5V driver
2019-12-03 Cleanup
2019-12-20 Fix reset circuit and other stuff
    This fixes the reset circuit and moves a few components. It also
    cleans up the BOM a bit.
    Also bumped to version 3.5.0
2019-12-21 Fixed solder mask settings
2019-12-21 Fixed unconnected trace and more solder mask adjustments.
2019-12-25 Moved WS2813B after fixing footprint v3.6
2019-12-27 Changed UART to CP2104 to simplify.
2019-12-29 Minor changes
    - Tweaked some of the component values in the 12V supply as per TI.
    - Removed unnecessary protection diode, the USB one is enough.
    - Changed UART to CS2104 which eliminates two resistors and is
    slightly cheaper
    - Updated PCB to reflect changes.
2020-05-04 Multiple changes from v3.7
    1. Fixed microphone so it uses the left channel
    2. Reduced the number of unique components, i.e. replacing a couple of
    resistor networks with already used resistors
    3. Removed unneeded resistor in programming circuit
    4. Moved speaker chip to the other side to be closer to the connector
    5. Cleaned up some of the traces and removed some inner-layer traces.

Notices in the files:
led-controller-wrover32/12v-booster.sch:
Copyright © 2018 by Aaron Williams
Copyright © 2019 by Aaron Williams
